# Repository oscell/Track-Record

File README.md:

## Team

| Name                | Responsibility                  | GUID     |
|---------------------|----------------------------------|----------|
| Oscar Meunier       | Network and Design engineer     | 2391076M |
| Sai Vamsi Karnam    | Development and Integration engineer          | 2805927K |
| Tara Duggan         | Electronics and Design engineer | 2363956D |
| Rohith Kambampati   | Backend developer and programmer               | 2782679K |

Track-Record is a face tracking system built on the Raspberry Pi 3B platform, using a Pi Camera Module and servo motors for real-time face detection and tracking. A GUI is also implemented which communicates via a server sending commands to the Raspberry Pi.

The full documentation can be found [here](https://tduggan63.github.io/Track-Record/index.html).

Find us on [Twitter](https://twitter.com/TrackrecordTeam) and [Instagram](https://www.instagram.com/_u/tracknrecordteam) to stay up to date with any of the latest developements or email us at tracknrecordteam@gmail.com to get in touch.

## Hardware

The following electronic components were used to build the project:

- [Raspberry Pi 3B](https://www.raspberrypi.com/products/raspberry-pi-3-model-b/)

- [SD Card] - One with a memory capacity of 16 gigs or more.
- [Pi Camera module 2](https://www.raspberrypi.com/products/camera-module-v2/)
- [SG92R Servo](https://www.towerpro.com.tw/product/sg92r-7/)

## Software Dependencies

The following libraries were used throughout the project:

- [CMake](https://cmake.org/download/)
- [OpenCV](https://opencv.org/releases/)
- [BCM2835](https://www.airspayce.com/mikem/bcm2835/index.html)
- [QT5](https://wiki.qt.io/Qt_for_Beginners)

## Installation and Usage

This project aims to build a standalone plug and play type product.
Clip the camera of your choice to the platform, switch the power on and watch it track you.
But wait there's more, you can build it on your own. Follow the instructions ahead.

## Instructions

- Step 1: Setting up the hardware
  - [Install the OS](https://www.raspberrypi.com/documentation/computers/getting-started.html) and set up a display.*
  - [Connect the Pi camera](https://www.raspberrypi.com/documentation/computers/compute-module.html#attaching-a-raspberry-pi-camera-module)
  - Connect the motors using the PinOut diagram: Pan at Gpio 18, Tilt at Gpio 17
  - 3D print the models -- Check the Schematics and Solidworks directories or build your own model

- Step 2: Software
  - Make sure to have the latest update for the GCC/G++ compiler on your Raspberry Pi OS.
  - [Setup cmake](https://cmake.org/download/) on your Raspberry Pi.
  - Clone the repo, the libraries used are included with the git package.
  
  ```git
  git clone https://github.com/oscell/Track-Record.git
  ```
  
  - Unpack the lib_package archive to /usr/include

  ```bash
  sudo tar -xf lib_package.tar.gz -C /usr/include
  ```
  
  - Create an executable in the `main/build` directory
    - Open a terminal and navigate to the main directory
    - Run the following commands to create the executable "tracknrecord"
  
    ```bash
    mkdir -p build && cd build
    cmake ..
    make
    ```

    - You should now see two executables named "tracknrecord" and "server" in the directory
  
  - Set executable permission to run on startup
    - Open a terminal and run the following commands
  
    ```bash
    mkdir /home/pi/.config/autostart
    nano /home/pi/.config/autostart/track.desktop
    ```

    - Copy or type the following text into the "track.desktop" file.
    - Replace the "directory" with the location of the executable named 'server.cpp' located in the main folder. (eg. home/pi/...)

    ```bash
    [Desktop Entry]
    Type=Application
    Name=Track
    Exec="directory"
    ```

    - Save the file using: Ctrl+X -> Y
  
- Step 3:
  - Setup the GUI* as shown in section 2 of the footnotes.

- Step 4:
  - Reboot the Pi from the terminal and it is ready to go.

    ```bash
    sudo reboot
    ```

  - The Pi should now be listening for commands.

  - Ensure the Pi and your personal machine are on the same network.

  - Open the GUI on your personal machine and click "start tracking".

  - To view the video feed, click the video feed button.

-----------------------------------------------------------------------------------------------------------------------------------------------------------------------

## *Footnotes  
  
### Section 1: Additonal information

- [Raspberry Pi PinOut diagram](https://www.raspberrypi.com/documentation/computers/raspberry-pi.html)
- SG92r wiring: Red for Power, Brown for Ground, and Yellow/Orange for Data.
- Set up [Raspberry Pi in headless mode](https://www.realvnc.com/en/blog/how-to-setup-vnc-connect-raspberry-pi/) without a display and other hardware.

### Section 2: GUI

This section should be built locally (not on the raspberry PI). It will be used to comunicate with the PI to send commands.

#### Dependencies

As previously with the raspi install [cmake](https://cmake.org/download/) on your machine. The next step is to install [Qt5](https://www.qt.io/download) although this can be done simply on linux using the command:

```bash
sudo apt-get install qt5-default
```

To find the path of your Qt5 installation, set up the C++, cmake, and QT5 on your personal machine and run the following command in the terminal:

```bash
find / -iname Qt5Config.cmake 2>/dev/null
```

Once you have the path, you can update the `/local/CMakeLists.txt` file with the correct Qt5_DIR.

```cmake
set(Qt5_DIR "/path/to/Qt5/lib/cmake/Qt5")
```

The comunication with the raspberry pi is done through a server. To find the IP adress of the raspery pi run in the raspberry pi terminal:

```bash
hostname -I
```

In `/local/src/GUI/main.cpp` change:

```c++
QString serverAddress = "127.0.0.1";
```

to

```c++
QString serverAddress = "<raspberry_pi_ip>"
```

### Build

```bash
cd local/
mkdir -p build && cd build
cmake ..
make
```

### Usage

### On the Raspi

Before being able to run send command the server must be initialised on the raspi.

```bash
cd main/build/
./server 
```

### On your local machine

Run the GUI.

```bash
 cd local/build/
./GUI1_0
```

It is comprised of a section for vieo feed input and 2 buttons.

### Tracking button

This sends a signal to the client which toggles the tracknrecord executable depending on the state it is currently in.

### Video feed

This toggles the user webcam to show how face detection and tracking works.
The GUI should look like this:

### Section 3: Testing

The test report and the code we used for tests is available on a different branch of this repo. It can be accessed using https://github.com/oscell/Track-Record/tree/tests/tests

### Section 4: 3D printing material

The Solidworks assemblies are provided in `Solidworks/`. This will require version 2022 or above however. To print the latest version of the stand `.stl` files are available in `Solidworks/Stls/`.

### Exploded view

***Note***: In out product demonstration the base used was the `Base_old` as we did not have time to 3D print such a large base.

Once assembled model looks like:

and in exploded view:

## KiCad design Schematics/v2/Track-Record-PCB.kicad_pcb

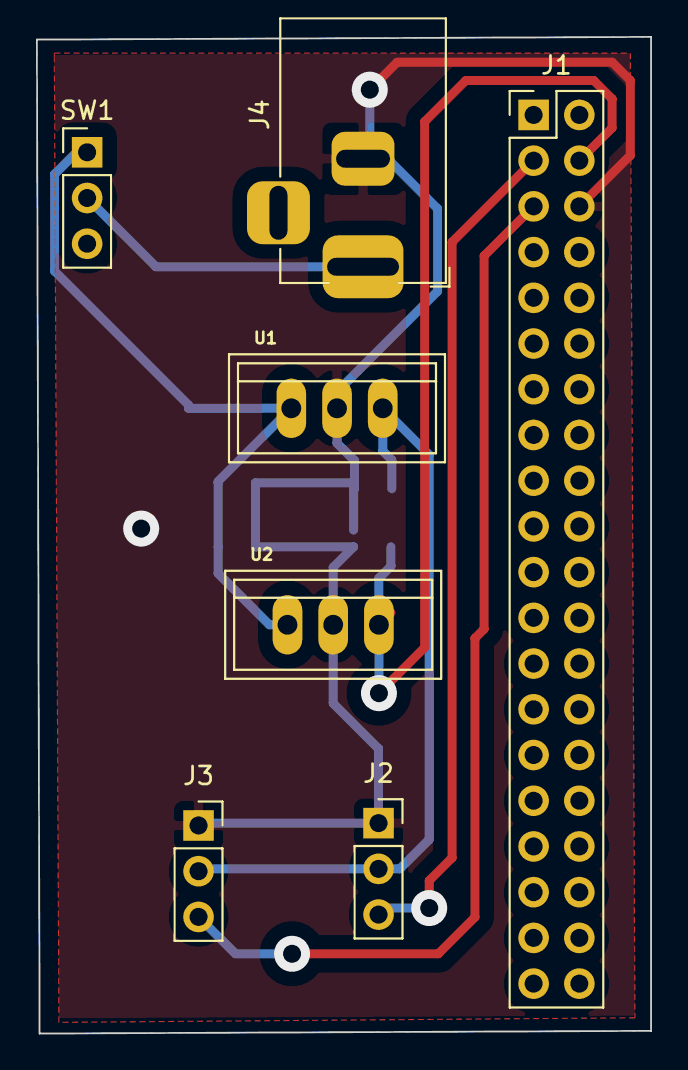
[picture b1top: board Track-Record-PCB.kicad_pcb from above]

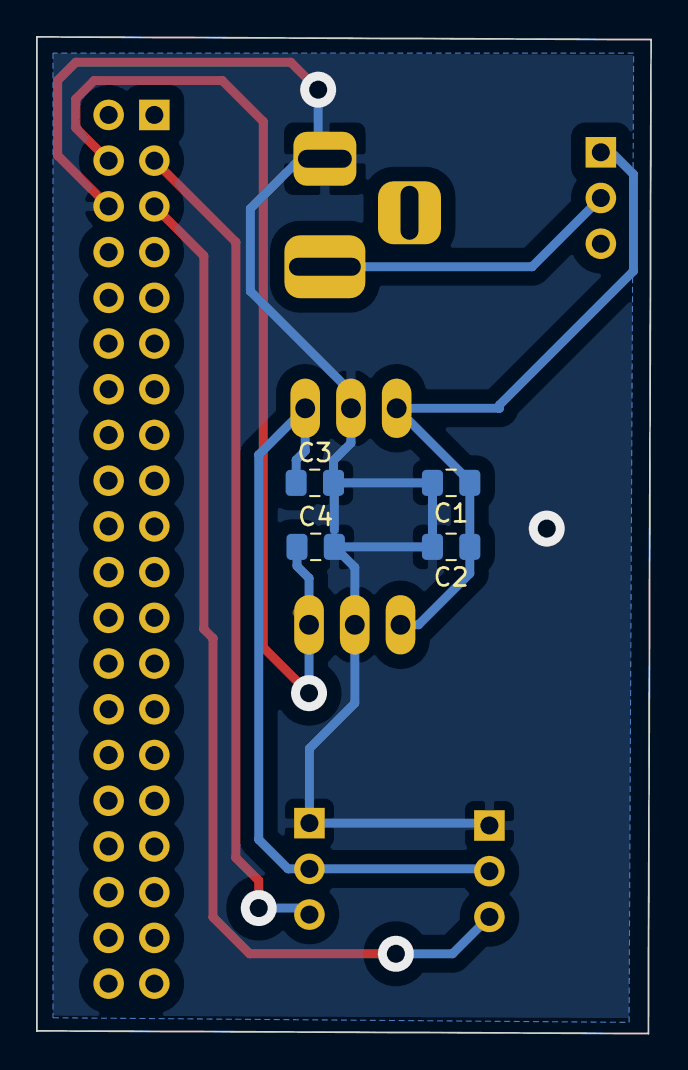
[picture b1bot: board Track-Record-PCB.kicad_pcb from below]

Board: 2 copper layers, 34.1 x 55.4 mm, 11 parts (4 on the bottom side), 7 nets.

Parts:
C1, C2: 0.33u; C_0805_2012Metric_Pad1.18x1.45mm_HandSolder
C3, C4: 0.1u; C_0805_2012Metric_Pad1.18x1.45mm_HandSolder
J1: RPI3_Connector; PinSocket_2x20_P2.54mm_Vertical
J2: Motor_1; PinSocket_1x03_P2.54mm_Vertical
J3: Motor_2; PinSocket_1x03_P2.54mm_Vertical
J4: 12V_connector; BarrelJack_Horizontal
SW1: Power Switch; PinHeader_1x03_P2.54mm_Vertical
U1, U2: L7805; TO-220-STANDING

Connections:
+5V: C3.1, J2.2, J3.2, U1.3
+5VD: C4.1, J1.4, U2.3
+12V: J4.1, SW1.2
+12VA: C1.1, C2.1, SW1.1, U1.1, U2.1
/Signal_1: J1.3, J2.3
/Signal_2: J1.5, J3.3
GND: C1.2, C2.2, C3.2, C4.2, J1.6, J2.1, J3.1, J4.2, U1.2, U2.2

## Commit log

2023-02-22 add drone test
2023-02-22 GPIO pinout reference
2023-03-01 Added Solidworks directory
2023-03-07 Added logo and improved read.md
2023-03-08 Face detection
2023-03-08 Helpful resources
2023-03-15 add power board schematics
2023-03-15 add schematics and PCB files
2023-03-16 Added source face detection using haar alt
2023-03-16 Added CMakeLists.txt
2023-03-16 Rename src to demo
2023-03-16 Added move.cpp
2023-03-16 Rename demo to demo.cpp
2023-03-20 Added basic GUI
2023-03-21 V3 Stls
2023-03-22 added server
2023-03-25 Add files via upload
    PCB files for UofG manufacture
2023-04-02 resvised solidworks designs
2023-04-03 added gui and server
2023-04-03 added paths
2023-04-06 fully working server
2023-04-07 Added Working GUI
2023-04-07 added GUI
2023-04-08 Create test
2023-04-08 Final code version 1
2023-04-08 Rename source to source.cpp
2023-04-09 Added old base
2023-04-11 Updated the code for pan motions
2023-04-11 updated with cmake file
2023-04-11 new source for pan motion
2023-04-11 fixed client
2023-04-11 configure Doxygen
2023-04-11 Delete .vscode directory
    Removing unnecessary directories
2023-04-11 Delete face detection directory
    Removing unnecessary directories
2023-04-11 Delete motor moving directory
    Removing redundant directories
2023-04-11 Delete source directory
    Removing redundant directories
2023-04-11 Delete source_v1 directory
    Removing redundant directories
2023-04-11 Delete source_v1_pan directory
    Removing redundant directories
2023-04-11 created motor class, header file, and added doxygen comment
2023-04-11 Create source.cpp
    Revised working code -- Functional
2023-04-11 adding doxygen output
2023-04-11 Added source.cpp
    Revised working code -- Functional
2023-04-11 updated doxygen configuration with added paths
2023-04-11 added description
2023-04-11 Software dependencies -- Stable
    Archive contains stable versions of OpenCV and BCM2835 libraries for C/C++
2023-04-11 Update README.md
    Added library usage details
2023-04-11 Added more Doxygen comments
2023-04-11 Renamed without space and created header file
2023-04-11 more Doxygen changes
2023-04-12 Refactored the code with classes
2023-04-12 Created CMakeLists.txt
2023-04-12 Added GUI and client/server
2023-04-12 Added styles to GUI
2023-04-13 Polishing up GUI
2023-04-13 polishing GUI
2023-04-13 old STL
2023-04-13 filenames
2023-04-13 Add Doxygen config file
2023-04-13 Add HTML and LaTeX documentation
2023-04-13 added Doxygen comments to code
2023-04-13 Updated Documentation
2023-04-13 added private to documentation
2023-04-13 Added main page
2023-04-13 test for github pages
2023-04-13 added documentation link to README
2023-04-13 Delete doxygen-doc directory
    moved to docs folder
2023-04-13 changed documentation output directory
2023-04-13 Fixed code formatting
2023-04-14 fixed CMakeList.txt
2023-04-14 Sorting GUI branch for version control
2023-04-14 Editing GUI read.md
2023-04-14 Finished GUI branch
2023-04-14 Finishing GUI read.md
2023-04-14 added better picture
2023-04-14 Removed old version
2023-04-14 added .gitignore
2023-04-14 ignoring build folders
2023-04-15 changes server adress
2023-04-15 added updated stls
2023-04-16 added tests directory and files
2023-04-16 updated cmake for tests
2023-04-16 updated tests
2023-04-17 Adding team roles
2023-04-17 Improved GUI variable names
2023-04-17 added a 3D printing material section
2023-04-17 updated docs
2023-04-17 Updated Readme.md with my guid
2023-04-17 Created a test cases file
2023-04-17 Created CMakeLists.txt for test code
2023-04-17 Created the test code move.cpp for testing
2023-04-17 changed wiki
2023-04-17 Add additional comments
2023-04-17 Updated readme with testing related details
2023-04-17 Updated readme with the testing details
2023-04-17 Updated readme with testing details
